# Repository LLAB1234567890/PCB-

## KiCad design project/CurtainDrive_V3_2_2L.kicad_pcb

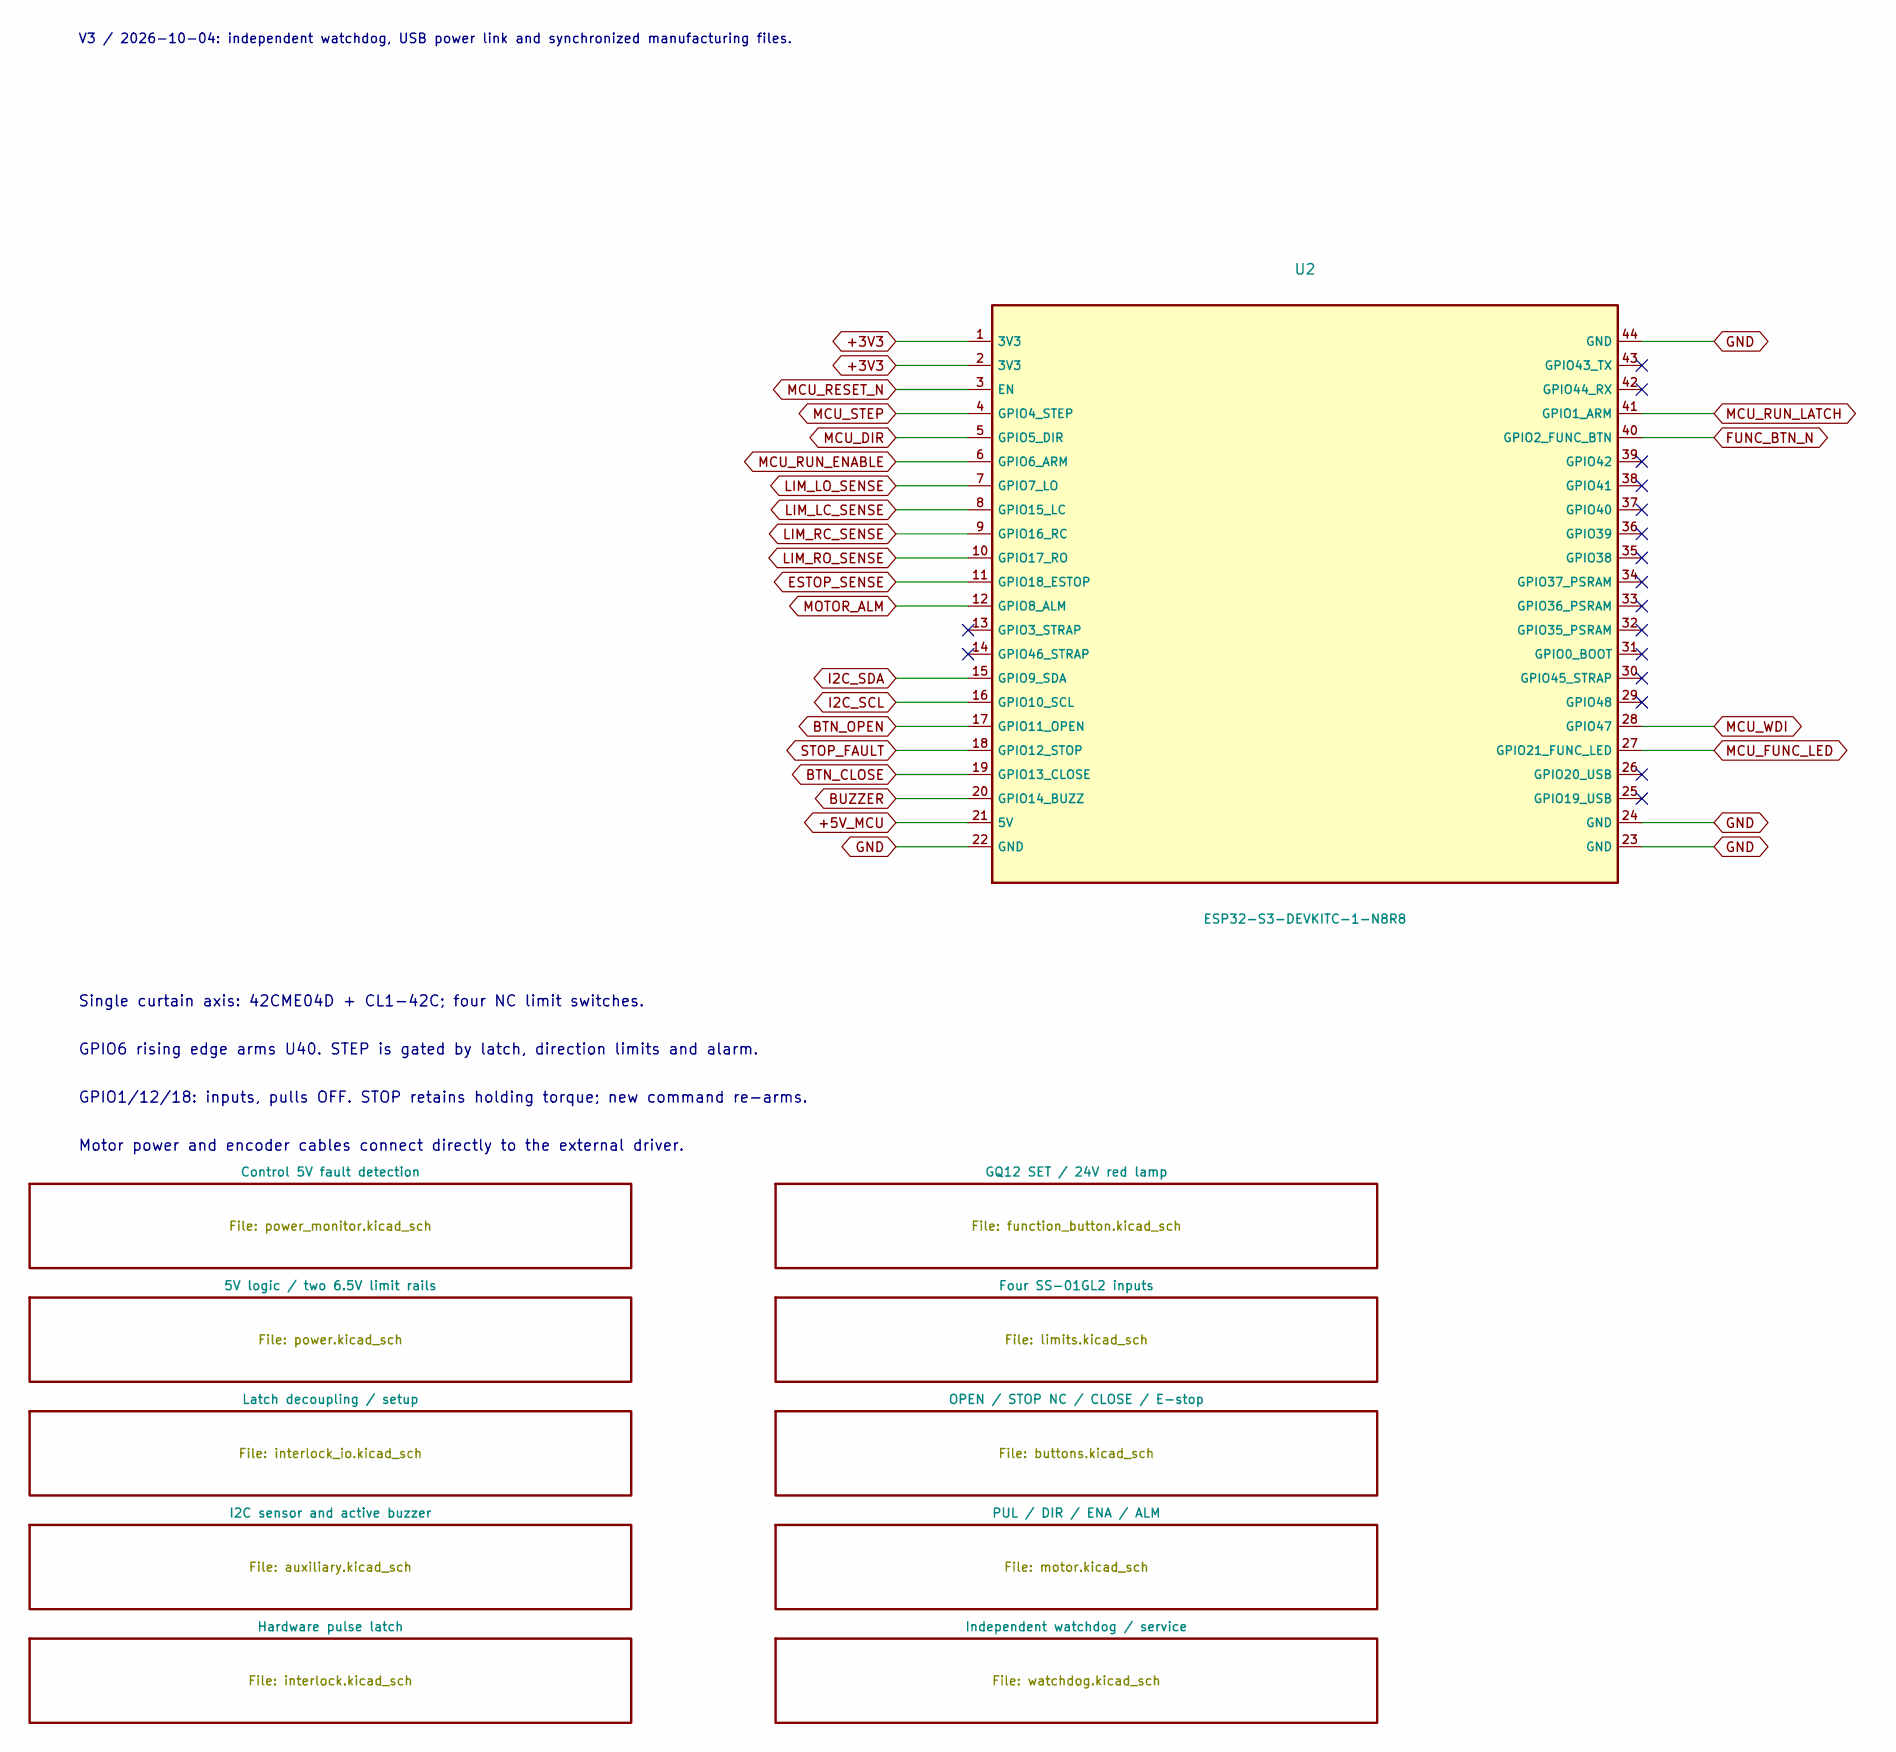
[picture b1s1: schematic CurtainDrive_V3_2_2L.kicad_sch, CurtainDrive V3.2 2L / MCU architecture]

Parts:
U2: ESP32-S3-DEVKITC-1-N8R8; ESP32_S3_DevKitC_1_N8R8; Manufacturer Part ESP32-S3-DEVKITC-1-N8R8

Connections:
+3V3: U2.1 (3V3), U2.2 (3V3); also elsewhere on the board
+5V_MCU: U2.21 (5V); also elsewhere on the board
BTN_CLOSE: U2.19 (GPIO13_CLOSE); also elsewhere on the board
BTN_OPEN: U2.17 (GPIO11_OPEN); also elsewhere on the board
BUZZER: U2.20 (GPIO14_BUZZ); also elsewhere on the board
ESTOP_SENSE: U2.11 (GPIO18_ESTOP); also elsewhere on the board
FUNC_BTN_N: U2.40 (GPIO2_FUNC_BTN); also elsewhere on the board
GND: U2.22 (GND), U2.23 (GND), U2.24 (GND), U2.44 (GND); also elsewhere on the board
I2C_SCL: U2.16 (GPIO10_SCL); also elsewhere on the board
I2C_SDA: U2.15 (GPIO9_SDA); also elsewhere on the board
LIM_LC_SENSE: U2.8 (GPIO15_LC); also elsewhere on the board
LIM_LO_SENSE: U2.7 (GPIO7_LO); also elsewhere on the board
LIM_RC_SENSE: U2.9 (GPIO16_RC); also elsewhere on the board
LIM_RO_SENSE: U2.10 (GPIO17_RO); also elsewhere on the board
MCU_DIR: U2.5 (GPIO5_DIR); also elsewhere on the board
MCU_FUNC_LED: U2.27 (GPIO21_FUNC_LED); also elsewhere on the board
MCU_RESET_N: U2.3 (EN); also elsewhere on the board
MCU_RUN_ENABLE: U2.6 (GPIO6_ARM); also elsewhere on the board
MCU_RUN_LATCH: U2.41 (GPIO1_ARM); also elsewhere on the board
MCU_STEP: U2.4 (GPIO4_STEP); also elsewhere on the board
MCU_WDI: U2.28 (GPIO47); also elsewhere on the board
MOTOR_ALM: U2.12 (GPIO8_ALM); also elsewhere on the board
STOP_FAULT: U2.18 (GPIO12_STOP); also elsewhere on the board

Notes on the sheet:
GPIO6 rising edge arms U40. STEP is gated by latch, direction limits and alarm.
Single curtain axis: 42CME04D + CL1-42C; four NC limit switches.
Motor power and encoder cables connect directly to the external driver.
GPIO1/12/18: inputs, pulls OFF. STOP retains holding torque; new command re-arms.
V3 / 2026-10-04: independent watchdog, USB power link and synchronized manufacturing files.

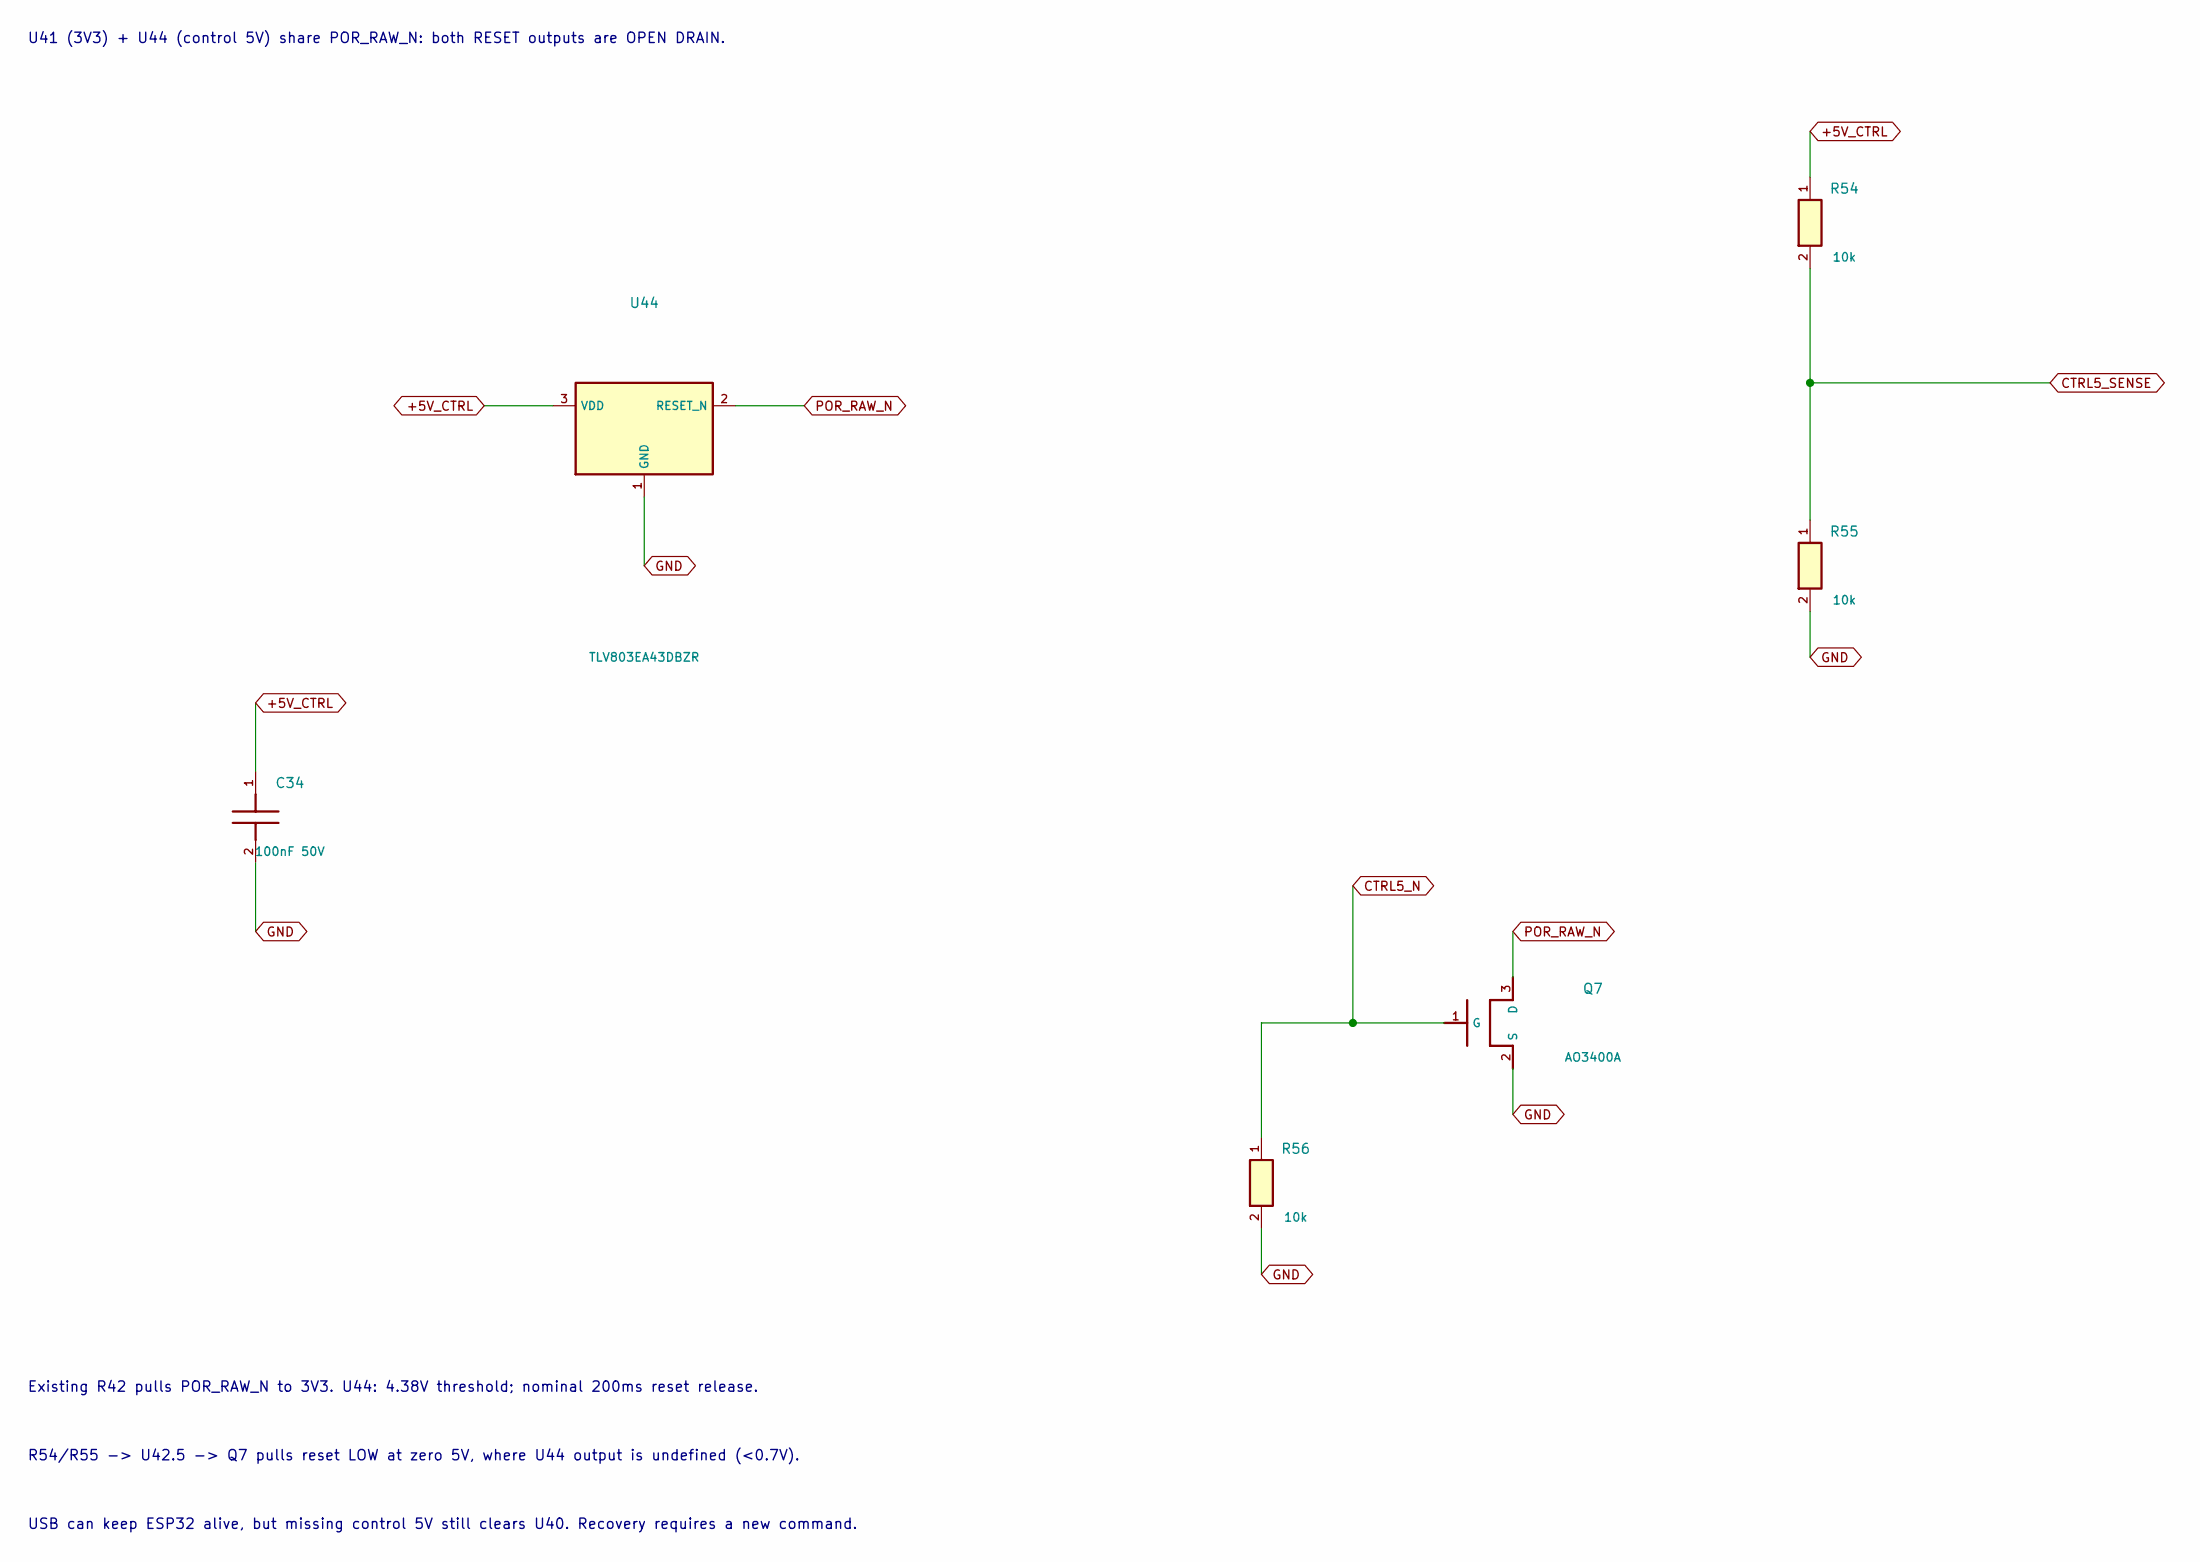
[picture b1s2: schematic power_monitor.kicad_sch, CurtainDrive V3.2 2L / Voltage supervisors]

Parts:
C34: 100nF 50V; C_0603_1608Metric; Voltage Rating 50V / X7R / 10%; Manufacturer Part CC0603KRX7R9BB104
Q7: AO3400A; SOT-23; Voltage Rating 30V / Vgs +/-12V; Manufacturer Part AO3400A
R54, R55, R56: 10k; R_0603_1608Metric; Voltage Rating 1% / 0.1W; Manufacturer Part 0603WAF1002T5E
U44: TLV803EA43DBZR; SOT-23; Voltage Rating 4.38V threshold / 200ms release / open 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; Manufacturer Part TLV803EA43DBZR

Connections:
+5V_CTRL: C34.1, R54.1, U44.3 (VDD); also elsewhere on the board
CTRL5_N: Q7.1 (G), R56.1; also elsewhere on the board
CTRL5_SENSE: R54.2, R55.1; also elsewhere on the board
GND: C34.2, Q7.2 (S), R55.2, R56.2, U44.1 (GND); also elsewhere on the board
POR_RAW_N: Q7.3 (D), U44.2 (RESET_N); also elsewhere on the board

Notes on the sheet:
R54/R55 -> U42.5 -> Q7 pulls reset LOW at zero 5V, where U44 output is undefined (<0.7V).
Existing R42 pulls POR_RAW_N to 3V3. U44: 4.38V threshold; nominal 200ms reset release.
U41 (3V3) + U44 (control 5V) share POR_RAW_N: both RESET outputs are OPEN DRAIN.
USB can keep ESP32 alive, but missing control 5V still clears U40. Recovery requires a new command.

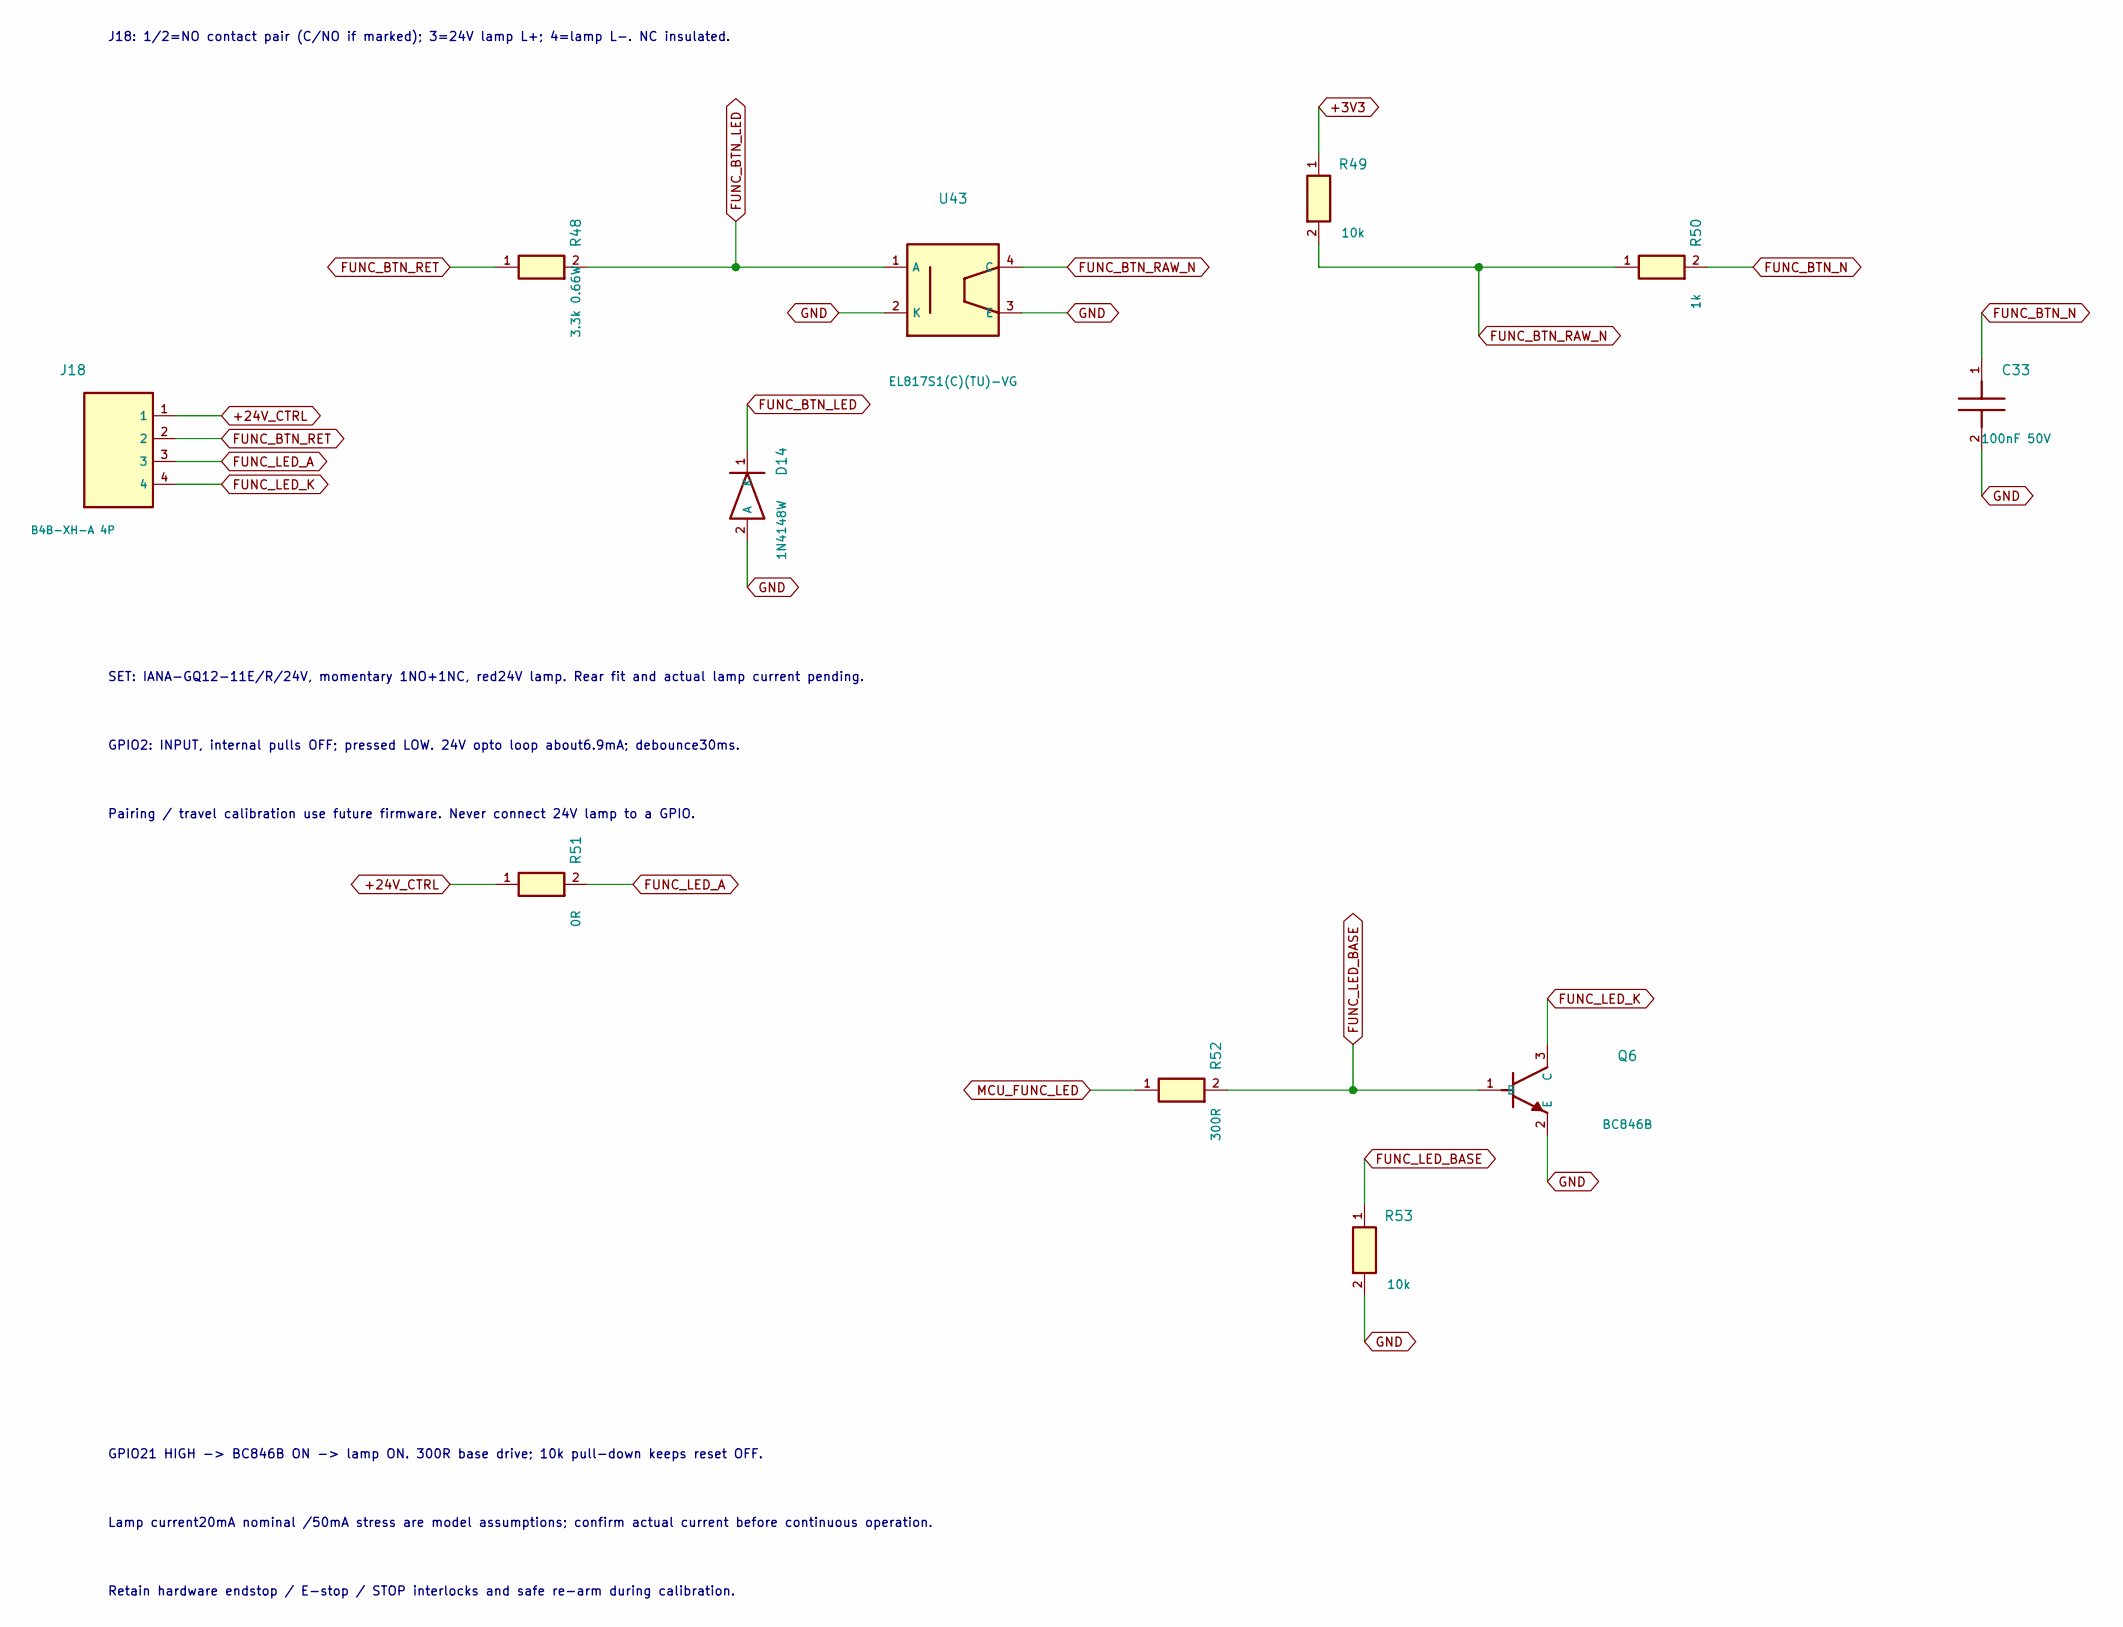
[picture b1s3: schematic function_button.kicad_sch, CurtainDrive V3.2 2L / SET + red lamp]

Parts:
C33: 100nF 50V; C_0603_1608Metric; Voltage Rating 50V / X7R / 10%; Manufacturer Part CC0603KRX7R9BB104
D14: 1N4148W; D_SOD-123; Manufacturer Part 1N4148W
J18: B4B-XH-A 4P; JST_XH_B4B-XH-A_1x04_P2.50mm_Vertical; Voltage Rating 3A / 250V; keyed 2.5mm; Manufacturer Part B4B-XH-A(LF)(SN)
Q6: BC846B; SOT-23; Voltage Rating 65V VCEO / 100mA absolute / SOT-23 B1 E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; Manufacturer Part BC846B,215
R48: 3.3k 0.66W; R_1206_3216Metric; Voltage Rating 1% / 0.66W at 70C / 1206; Manufacturer Part ERJ-UP8F3301V
R49, R53: 10k; R_0603_1608Metric; Voltage Rating 1% / 0.1W; Manufacturer Part 0603WAF1002T5E
R50: 1k; R_0603_1608Metric; Voltage Rating 1% / 0.1W; Manufacturer Part 0603WAF1001T5E
R51: 0R; R_0603_1608Metric; Voltage Rating 0R jumper / 0.1W / 1A maximum; Manufacturer Part RC0603JR-070RL
R52: 300R; R_0603_1608Metric; Voltage Rating 1% / 0.1W; Manufacturer Part RC0603FR-07300RL
U43: EL817S1(C)(TU)-VG; Source_U3; Manufacturer Part EL817S1(C)(TU)-VG

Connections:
+3V3: R49.1; also elsewhere on the board
+24V_CTRL: J18.1, R51.1; also elsewhere on the board
FUNC_BTN_LED: D14.1 (K), R48.2, U43.1 (A)
FUNC_BTN_N: C33.1, R50.2; also elsewhere on the board
FUNC_BTN_RAW_N: R49.2, R50.1, U43.4 (C)
FUNC_BTN_RET: J18.2, R48.1
FUNC_LED_A: J18.3, R51.2
FUNC_LED_BASE: Q6.1 (B), R52.2, R53.1
FUNC_LED_K: J18.4, Q6.3 (C)
GND: C33.2, D14.2 (A), Q6.2 (E), R53.2, U43.2 (K), U43.3 (E); also elsewhere on the board
MCU_FUNC_LED: R52.1; also elsewhere on the board

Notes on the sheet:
Retain hardware endstop / E-stop / STOP interlocks and safe re-arm during calibration.
Pairing / travel calibration use future firmware. Never connect 24V lamp to a GPIO.
SET: IANA-GQ12-11E/R/24V, momentary 1NO+1NC, red24V lamp. Rear fit and actual lamp current pending.
GPIO2: INPUT, internal pulls OFF; pressed LOW. 24V opto loop about6.9mA; debounce30ms.
J18: 1/2=NO contact pair (C/NO if marked); 3=24V lamp L+; 4=lamp L-. NC insulated.
GPIO21 HIGH -> BC846B ON -> lamp ON. 300R base drive; 10k pull-down keeps reset OFF.
Lamp current20mA nominal /50mA stress are model assumptions; confirm actual current before continuous operation.

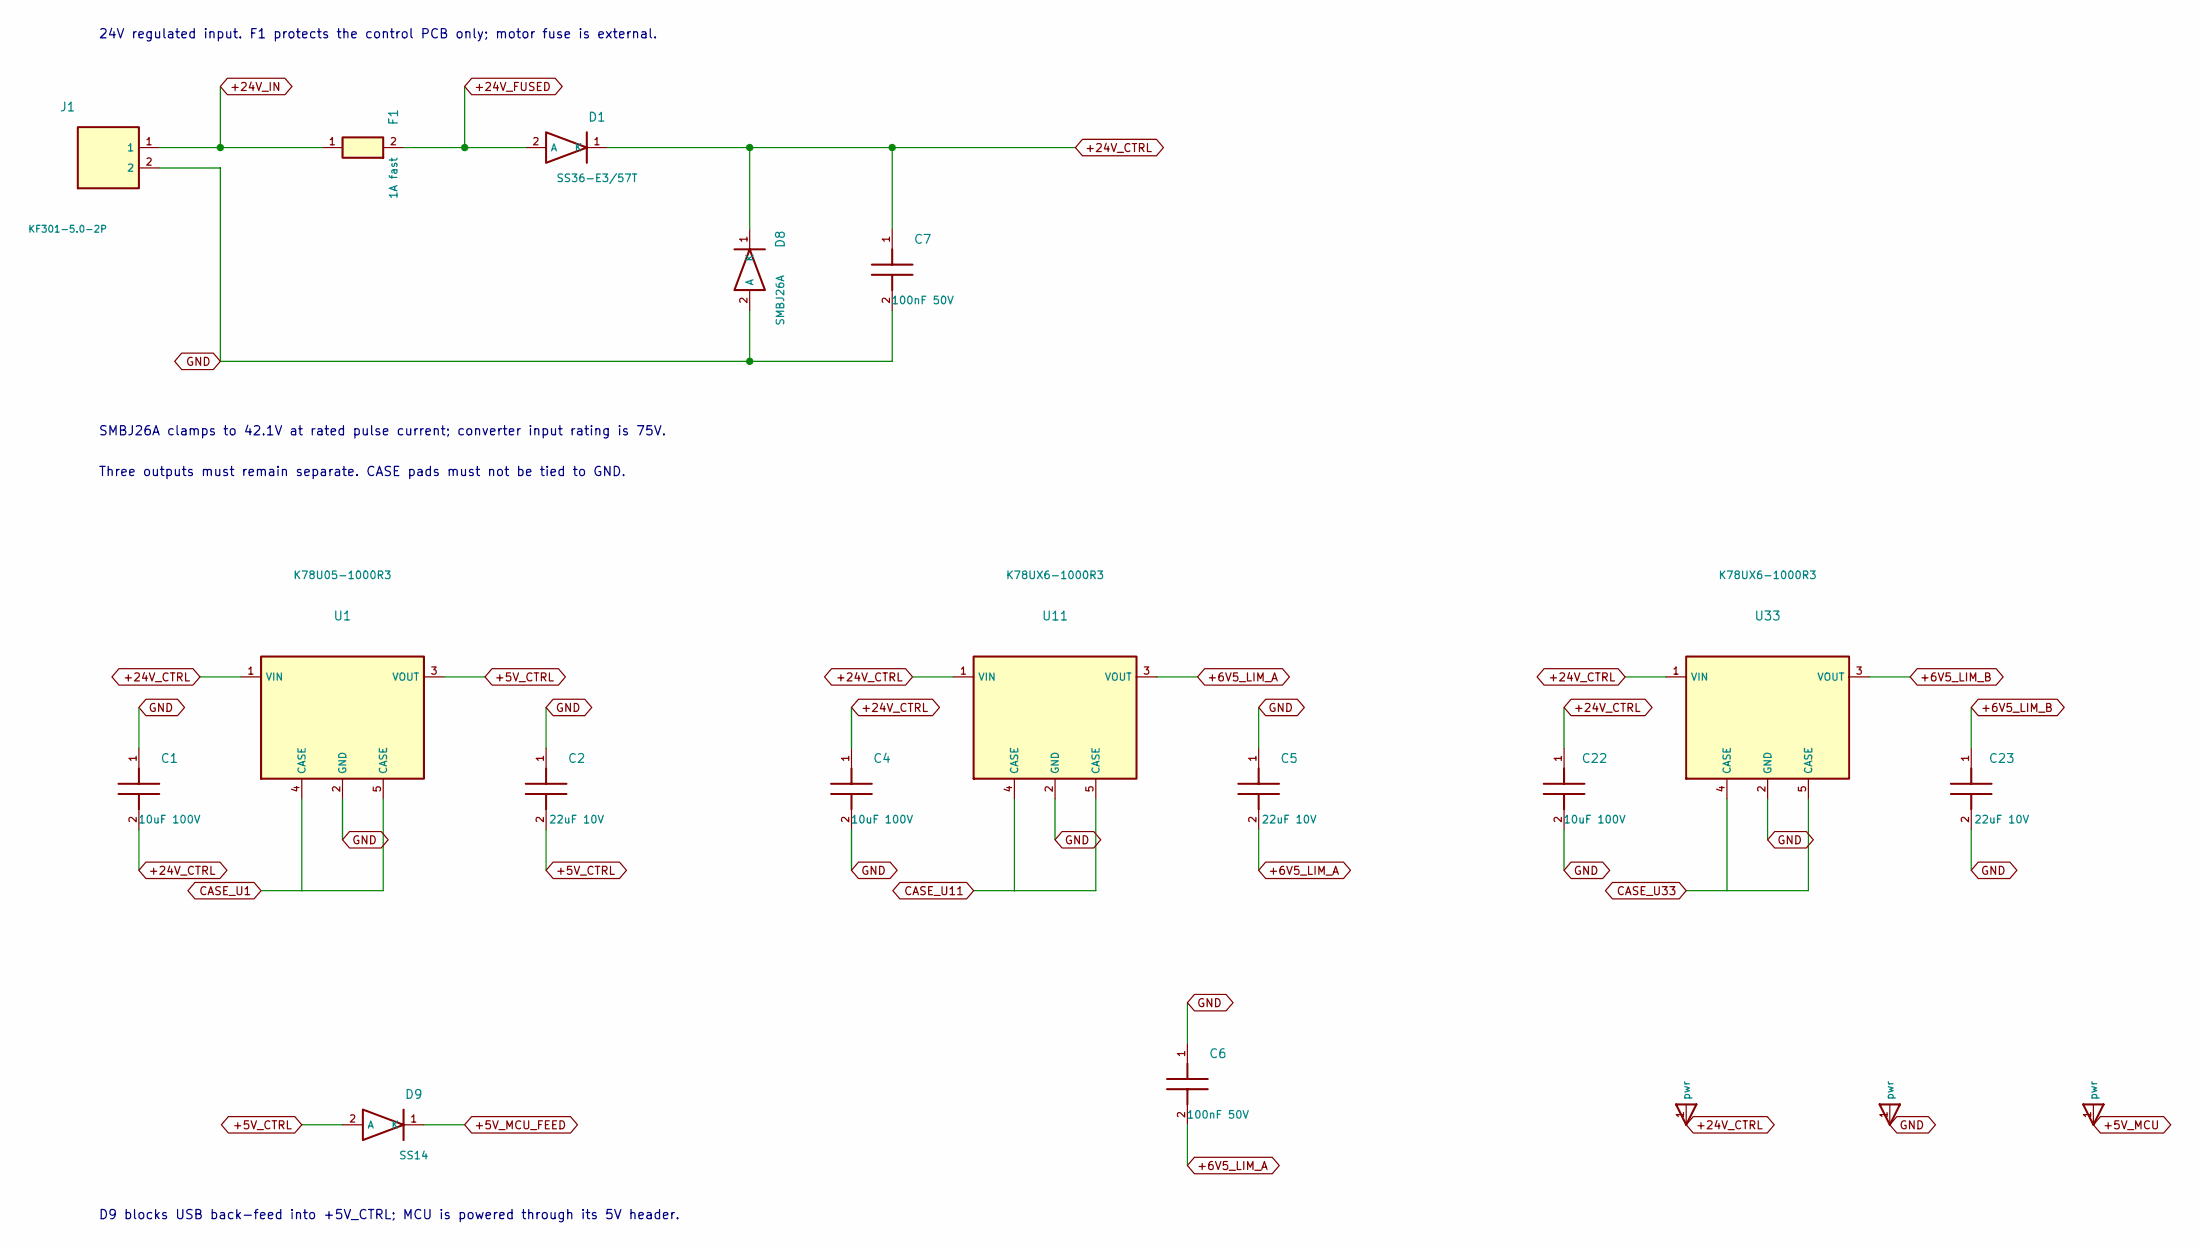
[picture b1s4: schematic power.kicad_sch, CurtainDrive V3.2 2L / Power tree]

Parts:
C1, C4, C22: 10uF 100V; C_1210_3225Metric; Voltage Rating 100V / X7R / 10%; Manufacturer Part C3225X7R2A106K250AC
C2, C5, C23: 22uF 10V; C_0805_2012Metric; Voltage Rating 10V / X5R / 20%; Manufacturer Part CL21A226MPQNNNE
C6, C7: 100nF 50V; C_0603_1608Metric; Voltage Rating 50V / X7R / 10%; Manufacturer Part CC0603KRX7R9BB104
D1: SS36-E3/57T; D_SMB; Voltage Rating 60V / 3A; Manufacturer Part SS36-E3/57T
D8: SMBJ26A; D_SMB; Voltage Rating 26V standoff / 42.1V clamp; Manufacturer Part SMBJ26A-13-F
D9: SS14; D_SMA; Voltage Rating 40V / 1A; Manufacturer Part SS14
F1: 1A fast; Source_F1; Voltage Rating 1A / 125V fast; Manufacturer Part 0451001.MRL
J1: KF301-5.0-2P; Source_J1; Manufacturer Part KF301-5.0-2P
U1: K78U05-1000R3; K78U05_1000R3; Voltage Rating 9-75V in / 5V 1A; Manufacturer Part K78U05-1000R3
U11, U33: K78UX6-1000R3; K78U05_1000R3; Voltage Rating 9-75V in / 6.5V 1A; Manufacturer Part K78UX6-1000R3

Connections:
+5V_CTRL: C2.2, D9.2 (A), U1.3 (VOUT); also elsewhere on the board
+5V_MCU_FEED: D9.1 (K); also elsewhere on the board
+6V5_LIM_A: C5.2, C6.2, U11.3 (VOUT); also elsewhere on the board
+6V5_LIM_B: C23.1, U33.3 (VOUT); also elsewhere on the board
+24V_CTRL: C1.2, C4.1, C7.1, C22.1, D1.1 (K), D8.1 (K), U1.1 (VIN), U11.1 (VIN), U33.1 (VIN); also elsewhere on the board
+24V_FUSED: D1.2 (A), F1.2
+24V_IN: F1.1, J1.1
CASE_U1: U1.4 (CASE), U1.5 (CASE)
CASE_U11: U11.4 (CASE), U11.5 (CASE)
CASE_U33: U33.4 (CASE), U33.5 (CASE)
GND: C1.1, C2.1, C4.2, C5.1, C6.1, C7.2, C22.2, C23.2, D8.2 (A), J1.2, U1.2 (GND), U11.2 (GND), U33.2 (GND); also elsewhere on the board

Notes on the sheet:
SMBJ26A clamps to 42.1V at rated pulse current; converter input rating is 75V.
Three outputs must remain separate. CASE pads must not be tied to GND.
D9 blocks USB back-feed into +5V_CTRL; MCU is powered through its 5V header.
24V regulated input. F1 protects the control PCB only; motor fuse is external.

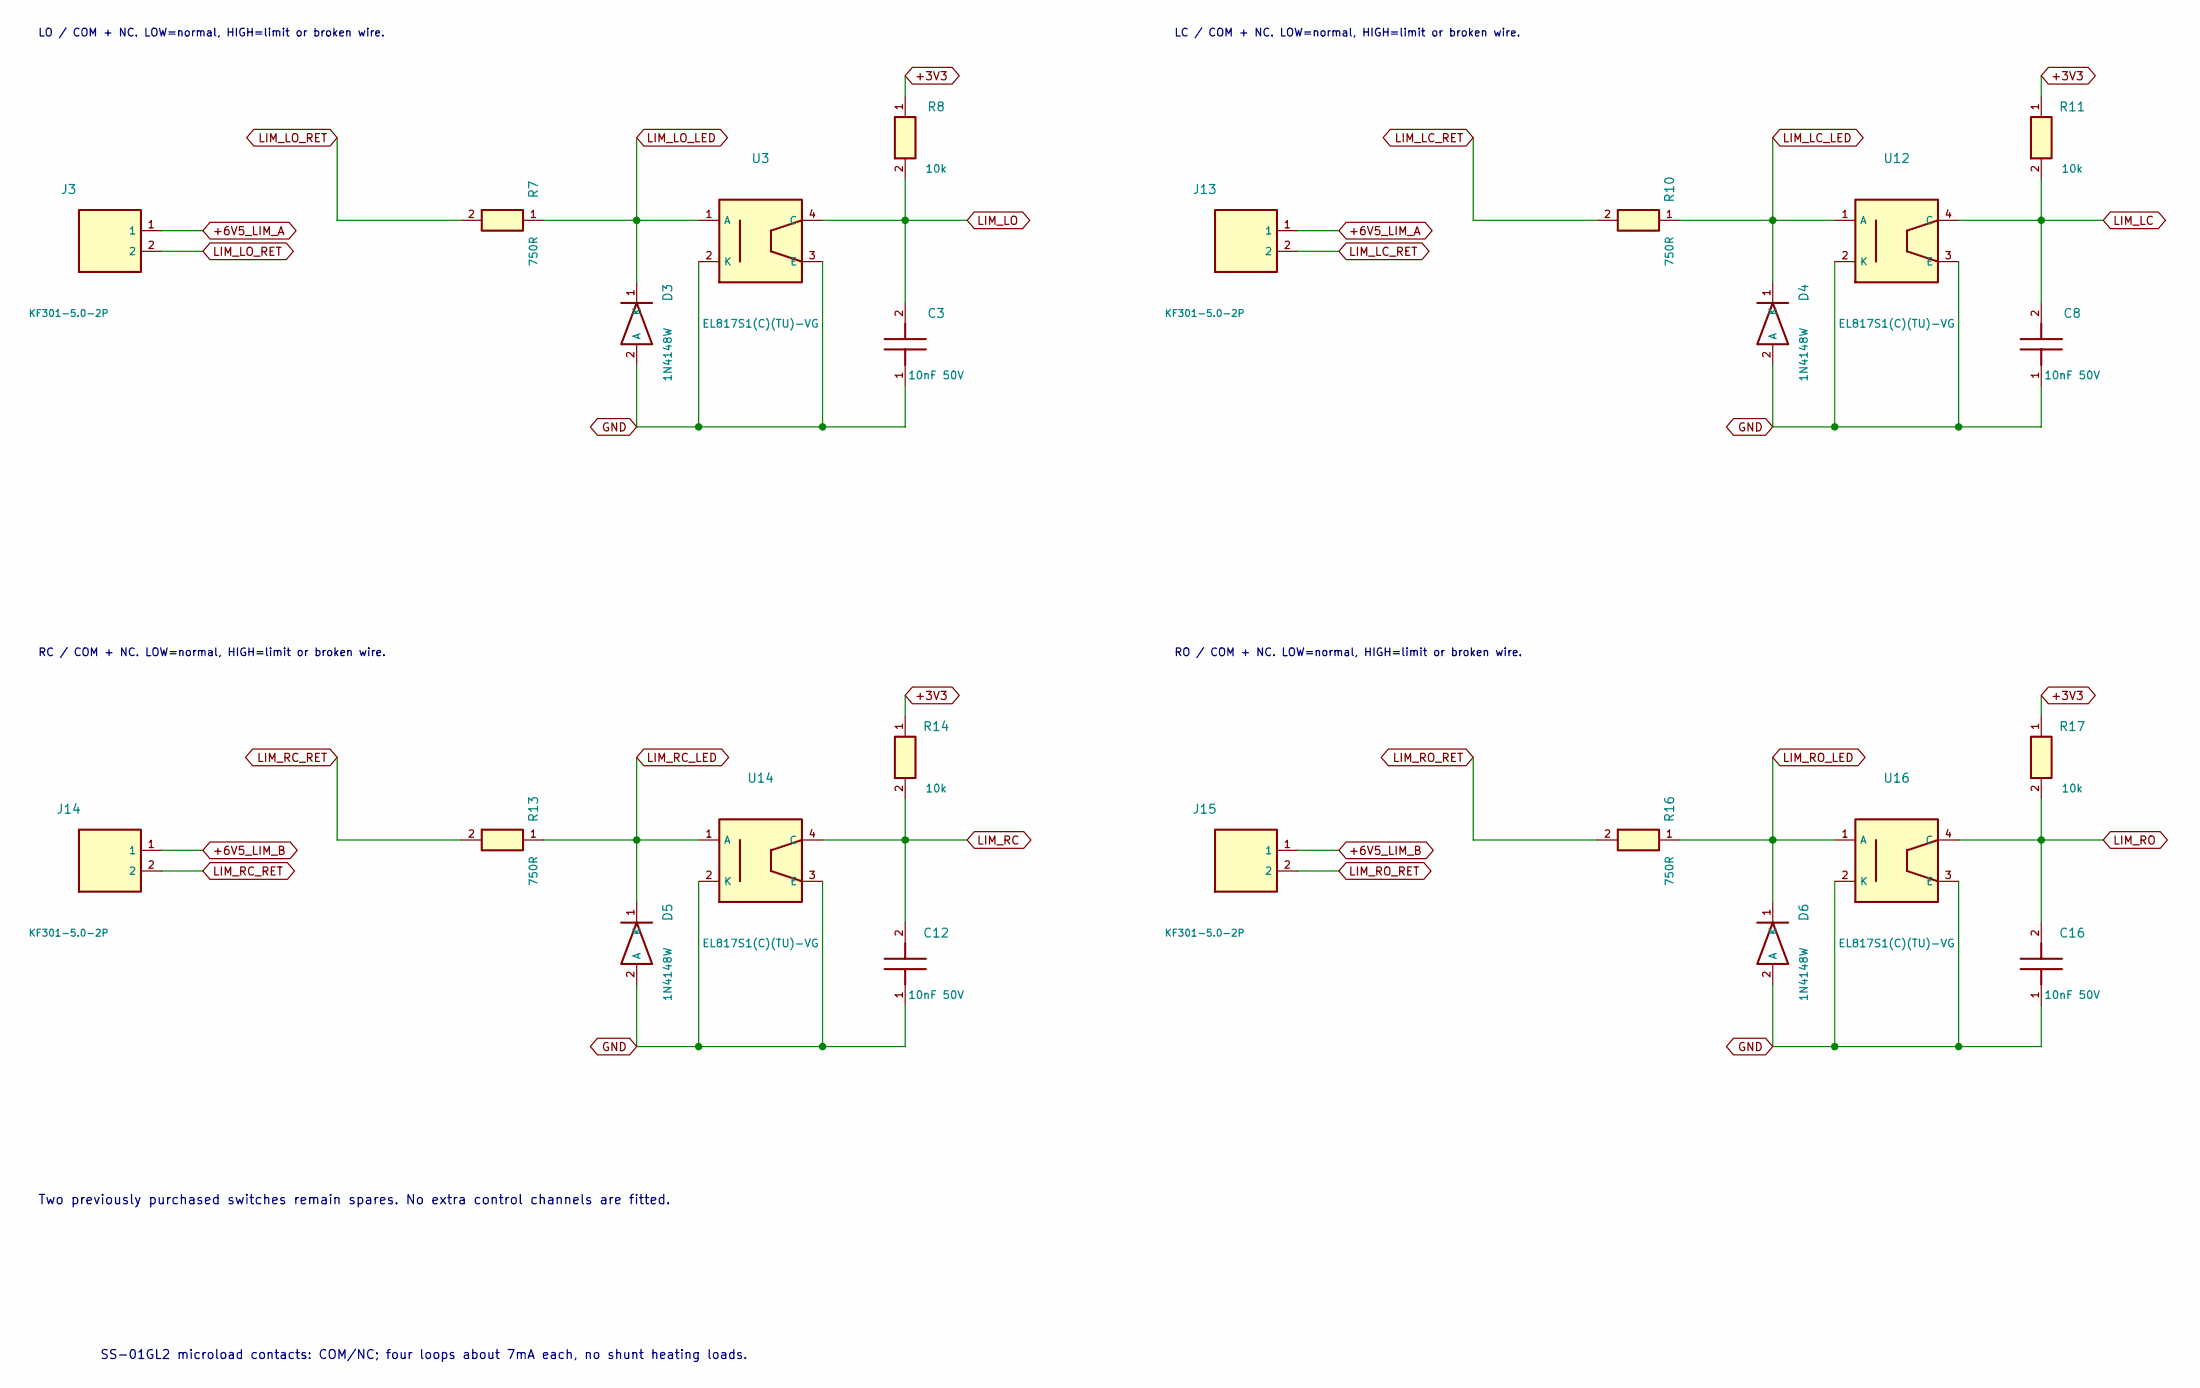
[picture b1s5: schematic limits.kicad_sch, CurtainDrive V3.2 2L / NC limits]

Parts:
C3, C8, C12, C16: 10nF 50V; C_0603_1608Metric; Voltage Rating 50V / X7R / 10%; Manufacturer Part 0603B103K500NT
D3, D4, D5, D6: 1N4148W; D_SOD-123; Manufacturer Part 1N4148W
J3: KF301-5.0-2P; Source_J3; Manufacturer Part KF301-5.0-2P
J13: KF301-5.0-2P; Source_J13; Manufacturer Part KF301-5.0-2P
J14: KF301-5.0-2P; Source_J14; Manufacturer Part KF301-5.0-2P
J15: KF301-5.0-2P; Source_J15; Manufacturer Part KF301-5.0-2P
R7, R10, R13, R16: 750R; R_0603_1608Metric; Voltage Rating 1% / 0.1W; Manufacturer Part 0603WAF7500T5E
R8, R11, R14, R17: 10k; R_0603_1608Metric; Voltage Rating 1% / 0.1W; Manufacturer Part 0603WAF1002T5E
U3: EL817S1(C)(TU)-VG; Source_U3; Manufacturer Part EL817S1(C)(TU)-VG
U12: EL817S1(C)(TU)-VG; Source_U12; Manufacturer Part EL817S1(C)(TU)-VG
U14: EL817S1(C)(TU)-VG; Source_U14; Manufacturer Part EL817S1(C)(TU)-VG
U16: EL817S1(C)(TU)-VG; Source_U16; Manufacturer Part EL817S1(C)(TU)-VG

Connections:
+3V3: R8.1, R11.1, R14.1, R17.1; also elsewhere on the board
+6V5_LIM_A: J3.1, J13.1; also elsewhere on the board
+6V5_LIM_B: J14.1, J15.1; also elsewhere on the board
GND: C3.1, C8.1, C12.1, C16.1, D3.2 (A), D4.2 (A), D5.2 (A), D6.2 (A), U3.2 (K), U3.3 (E), U12.2 (K), U12.3 (E), U14.2 (K), U14.3 (E), U16.2 (K), U16.3 (E); also elsewhere on the board
LIM_LC: C8.2, R11.2, U12.4 (C); also elsewhere on the board
LIM_LC_LED: D4.1 (K), R10.1, U12.1 (A)
LIM_LC_RET: J13.2, R10.2
LIM_LO: C3.2, R8.2, U3.4 (C); also elsewhere on the board
LIM_LO_LED: D3.1 (K), R7.1, U3.1 (A)
LIM_LO_RET: J3.2, R7.2
LIM_RC: C12.2, R14.2, U14.4 (C); also elsewhere on the board
LIM_RC_LED: D5.1 (K), R13.1, U14.1 (A)
LIM_RC_RET: J14.2, R13.2
LIM_RO: C16.2, R17.2, U16.4 (C); also elsewhere on the board
LIM_RO_LED: D6.1 (K), R16.1, U16.1 (A)
LIM_RO_RET: J15.2, R16.2

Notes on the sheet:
Two previously purchased switches remain spares. No extra control channels are fitted.
LC / COM + NC. LOW=normal, HIGH=limit or broken wire.
SS-01GL2 microload contacts: COM/NC; four loops about 7mA each, no shunt heating loads.
RC / COM + NC. LOW=normal, HIGH=limit or broken wire.
LO / COM + NC. LOW=normal, HIGH=limit or broken wire.
RO / COM + NC. LOW=normal, HIGH=limit or broken wire.
